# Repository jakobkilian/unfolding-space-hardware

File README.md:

# Unfolding Space Hardware

This repo contains the **hardware documentation of the “Unfolding Space” glove** – a prototypical open source navigation aid system for the visually impaired. 

Please check out the main repository of the [Unfolding Space](https://www.github.com/jakobkilian/unfolding-space) project for more information and a list of related repos anc content.

## Overall structure

In order to be able to use the Unfolding Space Glove, a relatively large amount of custom work is necessary. The following readme is only intended to give an overview of this and the contents of this repo. Note that not all details or design decisions are not documented here - if you really plan to build your own model, feel free to contact me if you have any questions.

The overall structure consists of 3 components:

- **5V USB power bank:** You can basically use any and wear it wherever you want. To keep the cable out of the way, I attached it to the upper arm with a sports arm band. I was using:
  - [Hama Power Pack *Supreme 10HD*](https://hama.com/00188307/hama-power-pack-supreme-10hd-10000mah). Raspis are picky about the supply voltage – if it drops too low (I think below 4.8 V), they reboot. Since they consume up to 3 A, the voltage of many batteries can easily drop below 5.0 V at peaks. Use high-quality power packs and 10 Ah to avoid this in advance or find one having stable output with > 4.9 V.
  - [SP Connect Running Band](https://sp-connect.com/collections/mounts/products/running-band) and a adhesive [Universal Interface](https://sp-connect.com/collections/phone-cases/products/universal-interface) was used to mount the power bank to the upper arm. Expensive but very reliable for this use case. There is tons of other, cheaper options out there.
- **USB-C Cable:** Here too, maintaining the voltage is crucial: use the shortest possible cable with good quality. The thickness of the insulation is a good indicator for low voltage drop, but only cutting and testing the copper wires can provide certainty. I had a 30 cm USB-A to USB-C cable from *Renkforce* in use (pictured), there may be plenty of others in your country.
- An finally **a) The Glove** hosting vibration motors and **b) the Unfolding Space Carrier Board** hosting the Raspberry Pi. See next sections.

### a) The Glove

The glove consists of two textile layers between which the motors are attached and the cables are laid. On the outside (back of the hand) there are Velcro fasteners and an IDC connector for attaching the carrier board. Currently there are two sizes, fitting most hand shapes and sizes. The production of the glove is relatively elaborate and is explained step by step in the [glove](glove) directory of this repo.

### b) Unfolding Space Carrier Board

The carrier board again consists of multiple components:

- The **Glove Connector** is implemented via an IDC connector soldered onto the PCB. *See [pcb](pcb)  directory for details and instructions.*
- The **ToF Camera** (a [Pico Flexx](https://pmdtec.com/picofamily/) camera from pmdtechnologies) is attached with a rubber band and a USB 3.0 Micro-B connector (originally this was a short cable), which is glued to the PCB. *See [pcb](pcb)  directory for details and instructions.*
- The **Raspberry Pi Compute Module 4** ([Link](https://www.raspberrypi.com/products/compute-module-4)) which serves as a computing unit. I used the CM4101016 configuration (16 GB Flash, 1 GB RAM, Wifi), a cheaper one (if available) would also do it as the app doesnt need much RAM.
- A **Cooling Fan for the CM4** was necessary because it became uncomfortably hot on warm days and passive cooling alone was not sufficient. At 24°C room temperature, the core temperature rose to >75°C without cooling, to ~67° with a small heat sink ([link](https://www.waveshare.com/cm4-heatsink.htm)) and to ~59°C with a larger one ([link](https://geekworm.com/products/cm4-12mm-aluminum-alloy-heatsink-c235?variant=33569307394136)). If you add a cooler to the latter ([link](https://geekworm.com/products/cm4-12mm-aluminum-alloy-heatsink-c235?variant=33569307426904)) or use [this smaller fan](https://www.waveshare.com/cm4-fan-3007.htm) (pictured) , it stays below 45°C. The last fan from Waveshare used in the picture operates with 12V and PWM. However, I used it without PWM and with 5V, which made it run very quietly.
- And then there is the **custom made PCB ** that carries the CM4 with two 100-pin mezzanine connectors, hosts the motors drivers, some electronics (gyro, compass, ...), the 5V USB-C power supply plug, the IDC connector to the glove and the USB connector to the ToF camera. ***See [pcb](pcb) directory for details and instructions.***

## Parts and Prices

There is a parts list / BOM with all components assembled on the root directory (called [bom-overall](bom-overall.csv)) which refers to further BOMs in directories [pcb](pcb) and [glove](glove). The total price of the overall structure is about $ 500, two thirds of which go to the ToF camera. Take a look at the BOMS for details.

## 3D Design

I did some 3D designs to check wheter the parts will fit and to dtermine size of the board etc. You can find them under [3D-design](3D-design), but note that they are not the final version (e.g. the cooling fan is not included) and they are for orientation only.

## Credits

Thanks to **[mattikra](https://github.com/mattikra)** and **[a2800276](https://github.com/a2800276)** from Press Every Key for helping me with the PCB design and ordering of the boards and parts!

Thanks to [dronecz](https://github.com/dronecz/Minimal_carrier_board_for_CM4)  and [timonsku](https://github.com/timonsku/Minimal-RPi-CM-4-Carrier) for some carrier board inspiration just after the CM4s were released.

Thanks to Shawn Hymel for providing a [tutorial on CM4 carrier boards](https://www.digikey.com/en/maker/projects/creating-a-raspberry-pi-compute-module-4-cm4-carrier-board-in-kicad/7812da347e5e409aa28d59ea2aaea490) and an exemplary KiCad template file (included in [pcb](pcb) , licensed under CC-BY-4.0)

Thanks to KiCad for providing Software and [Libraries](https://gitlab.com/kicad/libraries) for this project.

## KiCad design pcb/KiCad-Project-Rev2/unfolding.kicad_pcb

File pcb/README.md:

# Custom PCB: Unfolding Space Carrier Board Rev. 2

## PCB Design Files

You can find the **design files** in [KiCad-Project-Rev2](KiCad-Project-Rev2) and exports (**schematic, pcb layout, rendering**) in [exports](exports).

**Design rules** are based on the specifications of a *2-layer, complex, ENIG* board at aisler.net. Note that some of my rules thus are a bit unusual (e.g. clearance ≥ 0.1 mm or track width ≥ 0.2 mm; through whole ≥ 0.3mm). [See all specifications of Aisler here.](https://aisler.net/help/design-rules-and-specifications/design-rules) 

There also is a [Aisler project of the Rev. 2 board online](https://aisler.net/p/WSTOTZAR) if you are from Europe. Attention: the BOM / parts list needs to be updated to respective components by hand!

## BOM / parts list

See [bom-pcb](bom-pcb.csv) for a list with all needed parts for the pcb alone.

## Known issues

- Some parts (e.g. RGB LEDs, IMU and MMC) are very (very) small! We could successfully reflow them but it was quite a hustle.
- The RGB LEDs in the upper right corner are very bright in the current layout. We thus use GPIO pins of the raspi with pull-up resistor to drive them on lower light intensity. Consider changing the resistors on the board!
- The i2c multiplexer (PCA) is needed because the drv chips just have one i2c address. You could also use the drv2603 and use pwm to drive them. Writing on all 9 drvs with the multiplexer takes around 3ms. Not much time to save anyway...
- Shortly before dispatch, the pico-spox plug in the bottom left corner was added to drive a cooling fan with 5 V. Consider using a 4-pin plug and using pwm instead.

## Credits

Thanks to **[mattikra](https://github.com/mattikra)** and **[a2800276](https://github.com/a2800276)** from Press Every Key for helping me with the PCB design and ordering of the boards and parts!

Note the txt files in the directories of 3rd party assets for credits and licenses.

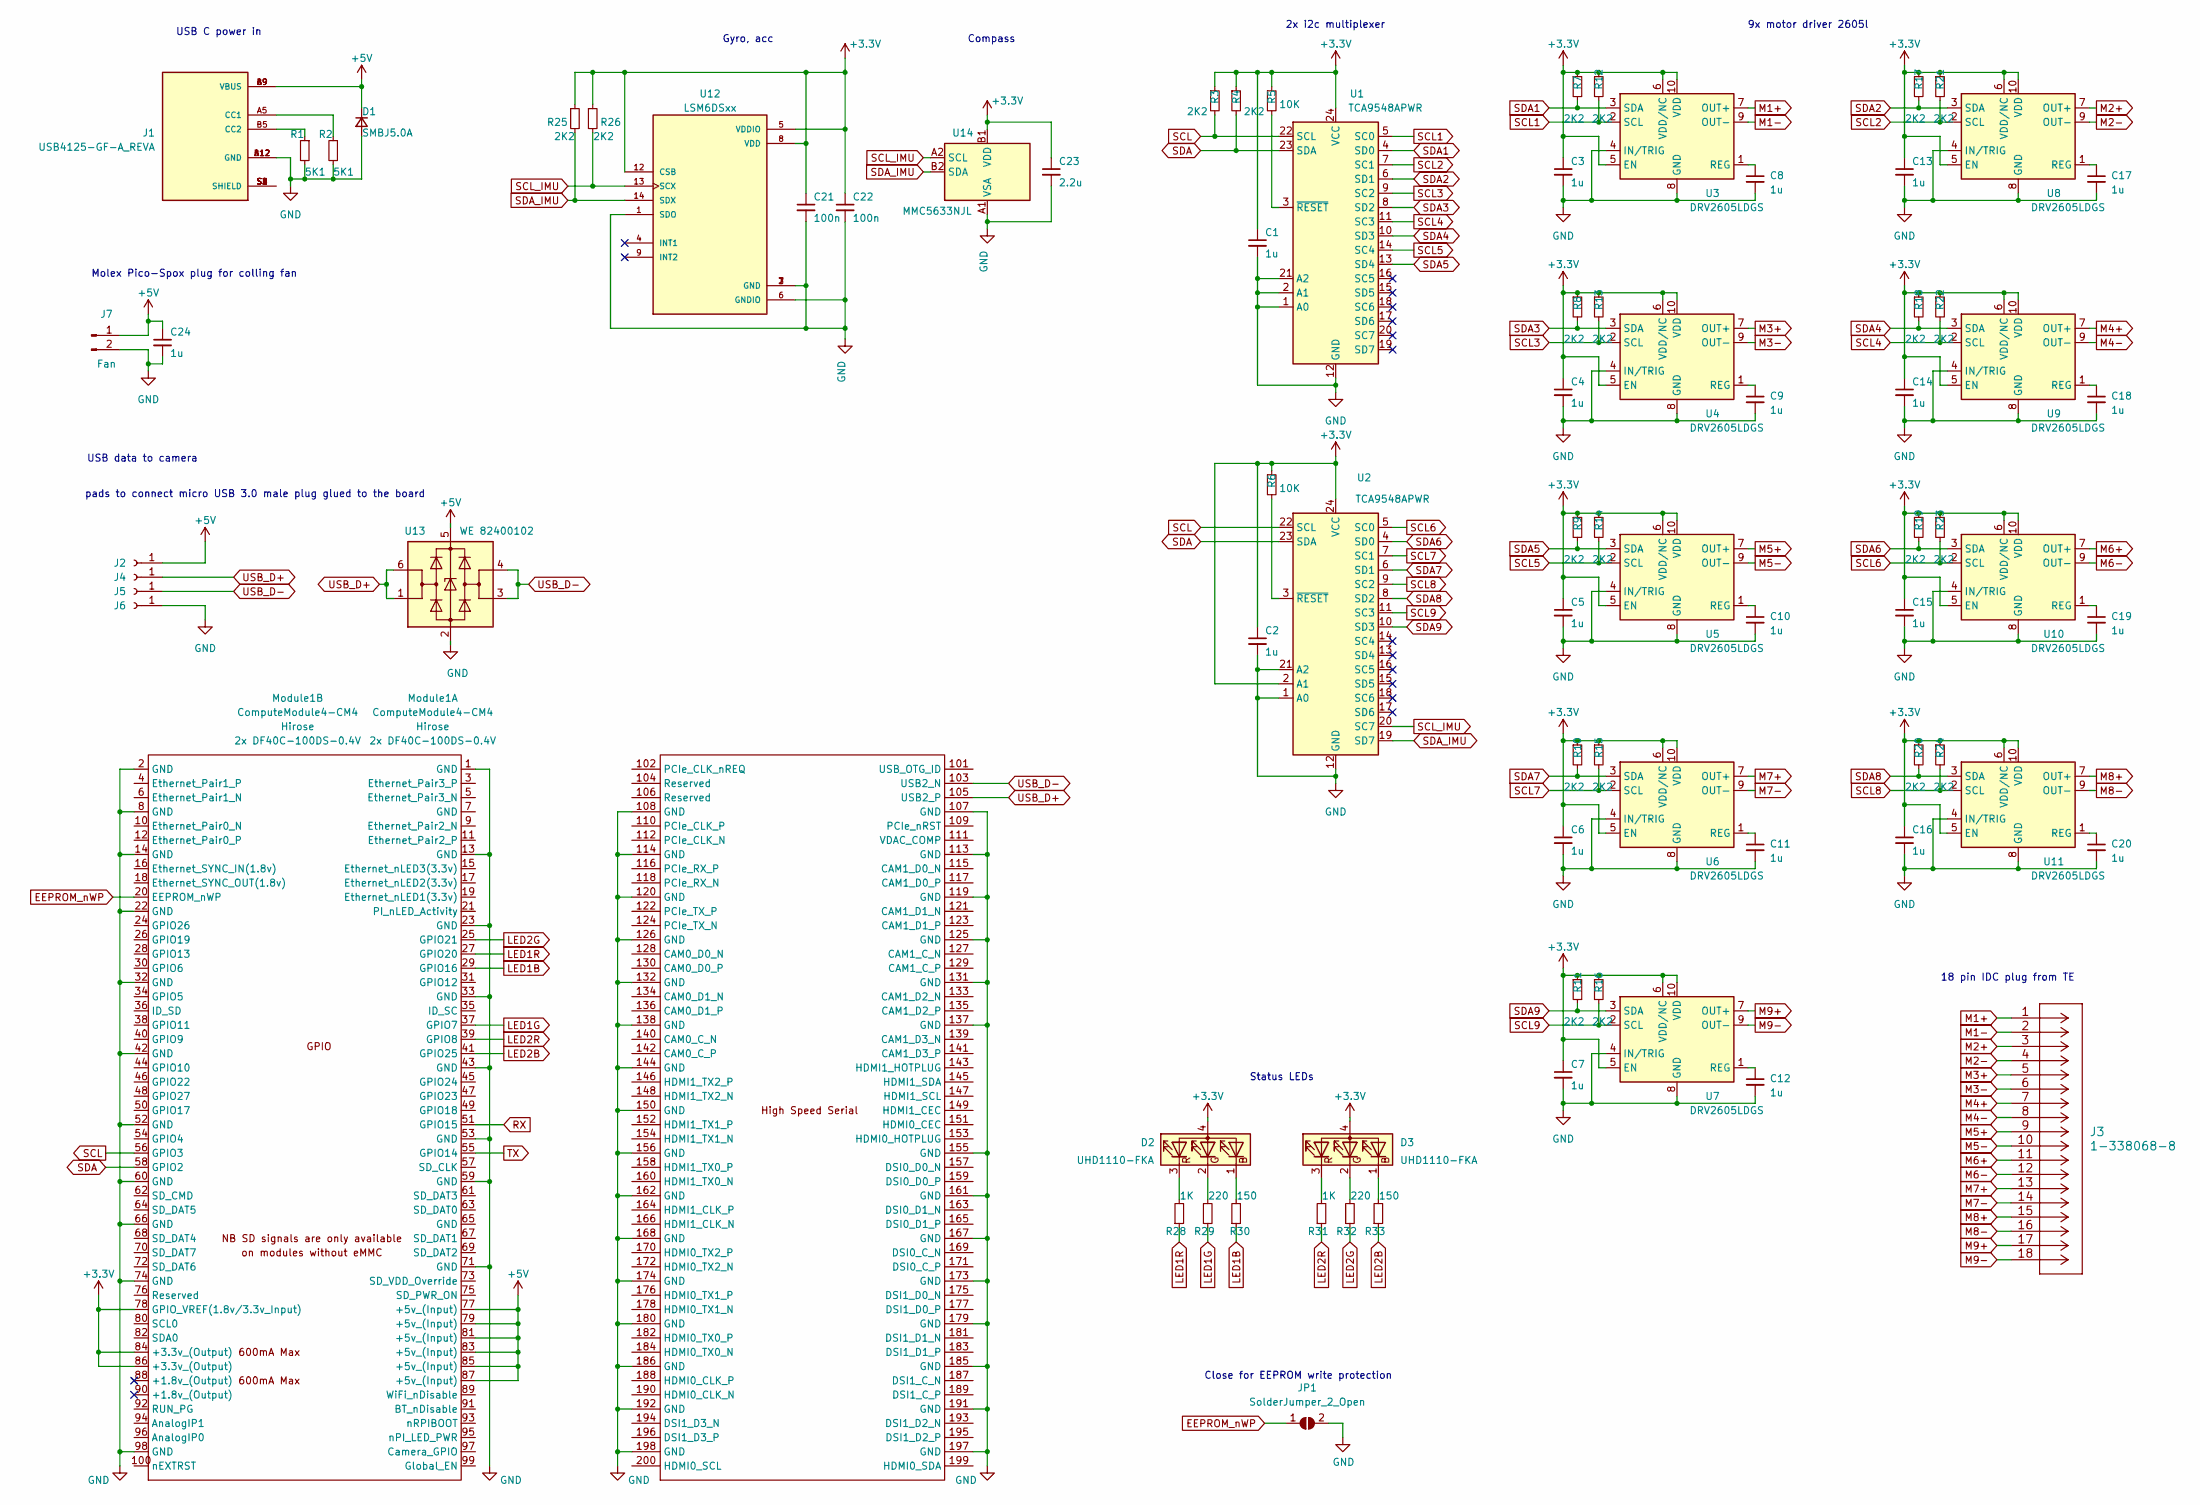
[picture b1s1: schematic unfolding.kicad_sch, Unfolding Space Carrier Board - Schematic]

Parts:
C1, C2, C3, C4, C5, C6, C7, C8, C9, C10, C11, C12, C13, C14, C15, C16, C17, C18, C19, C20, C24: 1u; C_0603_1608Metric
C21, C22: 100n; C_0603_1608Metric
C23: 2.2u; C_0603_1608Metric
D1: SMBJ5.0A; D_SMA
D2, D3: UHD1110-FKA
J1: USB4125-GF-A_REVA; GCT_USB4125-GF-A_REVA; PARTREV Rev A
J2, J4, J5, J6: Conn_01x01_Female; SolderWirePad_1x01_SMD_1x2mm
J3: 1-338068-8
J7: Fan; PICOspox-2-v
JP1: SolderJumper_2_Open; SolderJumper-2_P1.3mm_Open_RoundedPad1.0x1.5mm
Module1: ComputeModule4-CM4; Raspberry-Pi-4-Compute-Module
R1, R2: 5K1; R_0603_1608Metric
R3, R4, R7, R8, R9, R10, R11, R12, R13, R14, R15, R16, R17, R18, R19, R20, R21, R22, R23, R24, R25, R26: 2K2; R_0603_1608Metric
R5, R6: 10K; R_0603_1608Metric
R28, R31: 1K; R_0603_1608Metric
R29, R32: 220; R_0603_1608Metric
R30, R33: 150; R_0603_1608Metric
U1, U2: TCA9548APWR; TSSOP-24_4.4x7.8mm_P0.65mm
U3, U4, U5, U6, U7, U8, U9, U10, U11: DRV2605LDGS; VSSOP-10_3x3mm_P0.5mm
U12: LSM6DSxx; PQFN50P250X300X100-14N; PARTREV 1.2
U13: WE 82400102; SOT-23-6
U14: MMC5633NJL; WLP-4_0.86x0.86mm_P0.4mm

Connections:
+3V3: C1.1, C2.1, C3.1, C4.1, C5.1, C6.1, C7.1, C13.1, C14.1, C15.1, C16.1, C21.1, C22.1, C23.1, D2.4 (A), D3.4 (A), Module1.78 (GPIO_VREF(1.8v/3.3v_Input)), Module1.84 (+3.3v_(Output)), Module1.86 (+3.3v_(Output)), R3.1, R4.1, R5.1, R6.1, R7.1, R8.1, R9.1, R10.1, R11.1, R12.1, R13.1, R14.1, R15.1, R16.1, R17.1, R18.1, R19.1, R20.1, R21.1, R22.1, R23.1, R24.1, R25.1, R26.1, U1.24 (VCC), U2.2 (A1), U2.24 (VCC), U3.5 (EN), U3.6 (VDD/NC), U3.10 (VDD), U4.5 (EN), U4.6 (VDD/NC), U4.10 (VDD), U5.5 (EN), U5.6 (VDD/NC), U5.10 (VDD), U6.5 (EN), U6.6 (VDD/NC), U6.10 (VDD), U7.5 (EN), U7.6 (VDD/NC), U7.10 (VDD), U8.5 (EN), U8.6 (VDD/NC), U8.10 (VDD), U9.5 (EN), U9.6 (VDD/NC), U9.10 (VDD), U10.5 (EN), U10.6 (VDD/NC), U10.10 (VDD), U11.5 (EN), U11.6 (VDD/NC), U11.10 (VDD), U12.5 (VDDIO), U12.8 (VDD), U12.12 (CSB), U14.B1 (VDD)
+5V: C24.1, D1.1 (K), J1.A9 (VBUS), J1.B9 (VBUS), J2.1, J7.1, Module1.77 (+5v_(Input)), Module1.79 (+5v_(Input)), Module1.81 (+5v_(Input)), Module1.83 (+5v_(Input)), Module1.85 (+5v_(Input)), Module1.87 (+5v_(Input)), U13.5 (VBUS)
EEPROM_nWP: JP1.1 (A), Module1.20 (EEPROM_nWP)
GND: C1.2, C2.2, C3.2, C4.2, C5.2, C6.2, C7.2, C8.2, C9.2, C10.2, C11.2, C12.2, C13.2, C14.2, C15.2, C16.2, C17.2, C18.2, C19.2, C20.2, C21.2, C22.2, C23.2, C24.2, D1.2 (A), J1.A12 (GND), J1.B12 (GND), J6.1, J7.2, JP1.2 (B), Module1.1 (GND), Module1.2 (GND), Module1.8 (GND), Module1.13 (GND), Module1.14 (GND), Module1.22 (GND), Module1.23 (GND), Module1.32 (GND), Module1.33 (GND), Module1.42 (GND), Module1.43 (GND), Module1.52 (GND), Module1.53 (GND), Module1.59 (GND), Module1.60 (GND), Module1.66 (GND), Module1.71 (GND), Module1.74 (GND), Module1.98 (GND), Module1.107 (GND), Module1.108 (GND), Module1.113 (GND), Module1.114 (GND), Module1.119 (GND), Module1.120 (GND), Module1.125 (GND), Module1.126 (GND), Module1.131 (GND), Module1.132 (GND), Module1.137 (GND), Module1.138 (GND), Module1.144 (GND), Module1.150 (GND), Module1.155 (GND), Module1.156 (GND), Module1.161 (GND), Module1.162 (GND), Module1.167 (GND), Module1.168 (GND), Module1.173 (GND), Module1.174 (GND), Module1.179 (GND), Module1.180 (GND), Module1.185 (GND), Module1.186 (GND), Module1.191 (GND), Module1.192 (GND), Module1.197 (GND), Module1.198 (GND), R1.2, R2.2, U1.1 (A0), U1.2 (A1), U1.12 (GND), U1.21 (A2), U2.1 (A0), U2.12 (GND), U2.21 (A2), U3.4 (IN/TRIG), U3.8 (GND), U4.4 (IN/TRIG), U4.8 (GND), U5.4 (IN/TRIG), U5.8 (GND), U6.4 (IN/TRIG), U6.8 (GND), U7.4 (IN/TRIG), U7.8 (GND), U8.4 (IN/TRIG), U8.8 (GND), U9.4 (IN/TRIG), U9.8 (GND), U10.4 (IN/TRIG), U10.8 (GND), U11.4 (IN/TRIG), U11.8 (GND), U12.1 (SDO), U12.2 (GND), U12.3 (GND), U12.6 (GNDIO), U12.7 (GND), U13.2 (GND), U14.A1 (VSA)
LED1B: Module1.29 (GPIO16), R30.1
LED1G: Module1.37 (GPIO7), R29.1
LED1R: Module1.27 (GPIO20), R28.1
LED2B: Module1.41 (GPIO25), R33.1
LED2G: Module1.25 (GPIO21), R32.1
LED2R: Module1.39 (GPIO8), R31.1
M1+: J3.1, U3.7 (OUT+)
M1-: J3.2, U3.9 (OUT-)
M2+: J3.3, U8.7 (OUT+)
M2-: J3.4, U8.9 (OUT-)
M3+: J3.5, U4.7 (OUT+)
M3-: J3.6, U4.9 (OUT-)
M4+: J3.7, U9.7 (OUT+)
M4-: J3.8, U9.9 (OUT-)
M5+: J3.9, U5.7 (OUT+)
M5-: J3.10, U5.9 (OUT-)
M6+: J3.11, U10.7 (OUT+)
M6-: J3.12, U10.9 (OUT-)
M7+: J3.13, U6.7 (OUT+)
M7-: J3.14, U6.9 (OUT-)
M8+: J3.15, U11.7 (OUT+)
M8-: J3.16, U11.9 (OUT-)
M9+: J3.17, U7.7 (OUT+)
M9-: J3.18, U7.9 (OUT-)
unnamed: C8.1, U3.1 (REG)
unnamed: C9.1, U4.1 (REG)
unnamed: C10.1, U5.1 (REG)
unnamed: C11.1, U6.1 (REG)
unnamed: C12.1, U7.1 (REG)
unnamed: C17.1, U8.1 (REG)
unnamed: C18.1, U9.1 (REG)
unnamed: C19.1, U10.1 (REG)
unnamed: C20.1, U11.1 (REG)
unnamed: D2.1 (BK), R30.2
unnamed: D2.2 (GK), R29.2
unnamed: D2.3 (RK), R28.2
unnamed: D3.1 (BK), R33.2
unnamed: D3.2 (GK), R32.2
unnamed: D3.3 (RK), R31.2
unnamed: J1.A5 (CC1), R2.1
unnamed: J1.B5 (CC2), R1.1
unnamed: J1.S1 (SHIELD), J1.S2 (SHIELD), J1.S3 (SHIELD), J1.S4 (SHIELD)
unnamed: R5.2, U1.3 (~RESET)
unnamed: R6.2, U2.3 (~RESET)
RX: Module1.51 (GPIO15)
SCL: Module1.56 (GPIO3), R3.2, U1.22 (SCL), U2.22 (SCL)
SCL1: R12.2, U1.5 (SC0), U3.2 (SCL)
SCL2: R21.2, U1.7 (SC1), U8.2 (SCL)
SCL3: R13.2, U1.9 (SC2), U4.2 (SCL)
SCL4: R22.2, U1.11 (SC3), U9.2 (SCL)
SCL5: R14.2, U1.14 (SC4), U5.2 (SCL)
SCL6: R23.2, U2.5 (SC0), U10.2 (SCL)
SCL7: R15.2, U2.7 (SC1), U6.2 (SCL)
SCL8: R24.2, U2.9 (SC2), U11.2 (SCL)
SCL9: R16.2, U2.11 (SC3), U7.2 (SCL)
SCL_IMU: R26.2, U2.20 (SC7), U12.13 (SCX), U14.A2 (SCL)
SDA: Module1.58 (GPIO2), R4.2, U1.23 (SDA), U2.23 (SDA)
SDA1: R7.2, U1.4 (SD0), U3.3 (SDA)
SDA2: R17.2, U1.6 (SD1), U8.3 (SDA)
SDA3: R8.2, U1.8 (SD2), U4.3 (SDA)
SDA4: R18.2, U1.10 (SD3), U9.3 (SDA)
SDA5: R9.2, U1.13 (SD4), U5.3 (SDA)
SDA6: R19.2, U2.4 (SD0), U10.3 (SDA)
SDA7: R10.2, U2.6 (SD1), U6.3 (SDA)
SDA8: R20.2, U2.8 (SD2), U11.3 (SDA)
SDA9: R11.2, U2.10 (SD3), U7.3 (SDA)
SDA_IMU: R25.2, U2.19 (SD7), U12.14 (SDX), U14.B2 (SDA)
TX: Module1.55 (GPIO14)
USB_D+: J4.1, Module1.105 (USB2_P), U13.1 (I/O1), U13.6 (I/O1)
USB_D-: J5.1, Module1.103 (USB2_N), U13.3 (I/O2), U13.4 (I/O2)

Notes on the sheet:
Molex Pico-Spox plug for colling fan
Status LEDs
pads to connect micro USB 3.0 male plug glued to the board
Gyro, acc
USB C power in
Close for EEPROM write protection
USB data to camera
9x motor driver 2605l
2x i2c multiplexer
Compass
18 pin IDC plug from TE

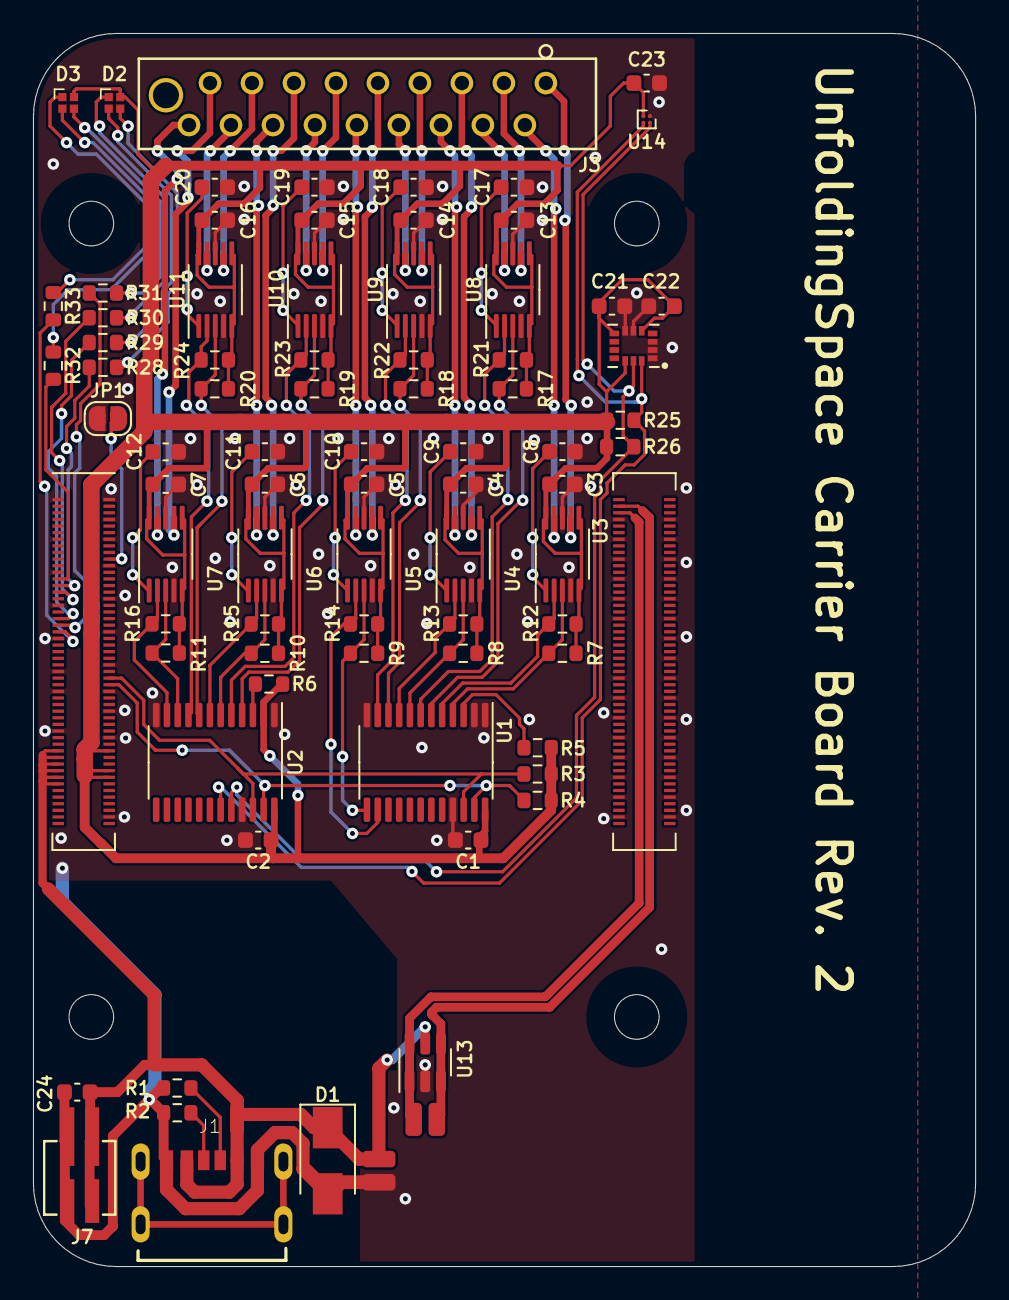
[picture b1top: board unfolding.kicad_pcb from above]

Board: 2 copper layers, 57.0 x 74.6 mm, 83 parts (0 on the bottom side), 72 nets.

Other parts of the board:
ToFCam-Stecker: ToFCam-Stecker; SteckerMicro-USB30-gewinkelt

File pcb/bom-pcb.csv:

Id,Designator,Package,Quantity,Designation,Description,Link,Est. Price Û
1,J3,https://www.digikey.de/de/products/detail/te-connectivity-am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,1,1-338068-8,IDC socket for glove connection,,1.5
2,C19;C15;C10;C13;C9;C5;C16;C14;C12;C24;C4;C2;C1;C3;C8;C20;C17;C18;C11;C6;C7,C_0603_1608Metric,21,1u,capacitor,,1
3,C21;C22,C_0603_1608Metric,2,100n,capacitor,,0
4,C23,C_0603_1608Metric,1,2.2u,capacitor,,0
5,D1,D_SMA,1,SMBJ5.0A,ESD for USB-C power supply,,0.5
6,J1,GCT_USB4125-GF-A_REVA,1,USB4125-GF-A_REVA,USB-C power supply socket,,0.5
7,ToFCam-Stecker,Micro-USB30-Plug,1,System-S USB 3.0 cable,glued USB plug,https://www.system-s.com/USB-3-0-Micro-B/SYSTEM-S-Micro-USB-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,9
8,J7,PICOspox-2-v,1,PICOspox-2-v,cooling fan plug,,0.5
9,U12,PQFN50P250X300X100-14N,1,LSM6DSxx,IMU / Accelerometer and Gyroscope,,5
10,R28;R31,R_0603_1608Metric,2,1K,resistor,,0
11,R18;R19;R17;R7;R11;R13;R16;R3;R20;R9;R22;R26;R15;R24;R10;R25;R12;R4;R23;R8;R14;R21,R_0603_1608Metric,22,2K2,resistor,,1
12,R29;R32,R_0603_1608Metric,2,220,resistor,,0
13,R33;R30,R_0603_1608Metric,2,150,resistor,,0
14,R6;R5,R_0603_1608Metric,2,10K,resistor,,0
15,R1;R2,R_0603_1608Metric,2,5K1,resistor,,0
19,U13,SOT-23-6,1,WE 82400102,TVS diode for USB data (camera),,1
20,U2;U1,TSSOP-24_4.4x7.8mm_P0.65mm,2,TCA9548APWR,i2c multiplexer,,7
21,D3;D2,UHD1110-FKA,2,UHD1110-FKA,RGB LED,,0.5
22,U3;U5;U10;U8;U4;U11;U9;U7;U6,VSSOP-10_3x3mm_P0.5mm,9,DRV2605LDGS,motor driver,,33
23,U14,WLP-4_0.86x0.86mm_P0.4mm,1,MMC5633NJL,compass,,1.5
24,-,,2,DF40HC(3.0)-100DS-0.4V(51,100pin mezzanine connector for CM4,https://www.mouser.de/ProductDetail/Hirose-Connector/DF40HC3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,4
25,-,,1,,Board production,,10
,,,,,,SUM,76

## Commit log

2021-03-30 First version, rudimentary schematics and layout
2021-03-30 gitignore change
2021-04-02 Change Folder Structure. Move PCB files to "carrier-pcb"
2021-04-02 Add folder for overall design of computing unit in CAD. Add part models
2021-04-02 Add usb plug. Add fusion archive. Delete GrabCAD file – identical to raspi.org step file
2021-04-12 Add camera clamp and heatsink
2021-04-19 Add 3rd_party_libs folder and place footrpints and symbols. Place bmx160 and TE IDC connector. Add route_try file to try out routing.
2021-04-19 Add models for plug. Add new export
2021-04-21 Route everything in route_try file
2021-04-23 New routing
2021-04-23 finish new routing with diff pair. export stp file.
2021-04-26 reroute usb traces. make motor traces thicker. small changes
2021-04-26 add roundings, add BOM
2021-04-29 change diode footprint
2021-04-30 change ESD protection. change usb plug. reroute
2021-05-23 Bestellte Version
2021-06-28 Added compass, added LEDs, changed USB TVS diode, fixed power TVS diode direction, moved accelerometer, misc minor improvements
2021-06-28 Added Pico-SPOX connector for 5V fan
2021-06-29 Add milling for camera fixation rubber band. Add silkscreen text "UnfoldingSpace Carrier Board Rev. 2"
2021-06-29 deleted and ignored backups
2021-06-29 removed more backups and renamed files. USE MORE BRANCHES, DONT RENAME
2021-06-29 Changed RGB LED footprints
2021-06-29 Re-add non plated sot for rubber band for fixation of camera
2021-06-29 edit slot to min width of 1,6mm of aisler.net
2021-06-30 Lock Slot from last commit
2021-07-04 Add general docs folder (also for parts that are not on the pcb). Add chips and parts that are going to be used in rev 2 (v0.2)
2021-08-04 consolidated docs into single dir
2022-01-14 Restructure directories. New KiCad Verison + File. License notes. Add BOMs. Start documenting pcb
2022-01-14 update main readme and bom
2022-01-14 move images directory to /images
2022-01-14 Update Glove instructions
2022-01-14 Reducing repo size
2022-01-14 correct faulty links
2022-01-14 update faulty links
2022-01-14 update links to be relative
2022-01-14 Edit all BOMs - put links behind price
2022-01-14 Add LICENSE
2022-01-14 Update LICENSE
2024-04-22 layout

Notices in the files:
pcb/KiCad-Project-Rev2/unfolding.kicad_pcb:
Copyright (c) 2022 Jakob Kilian
